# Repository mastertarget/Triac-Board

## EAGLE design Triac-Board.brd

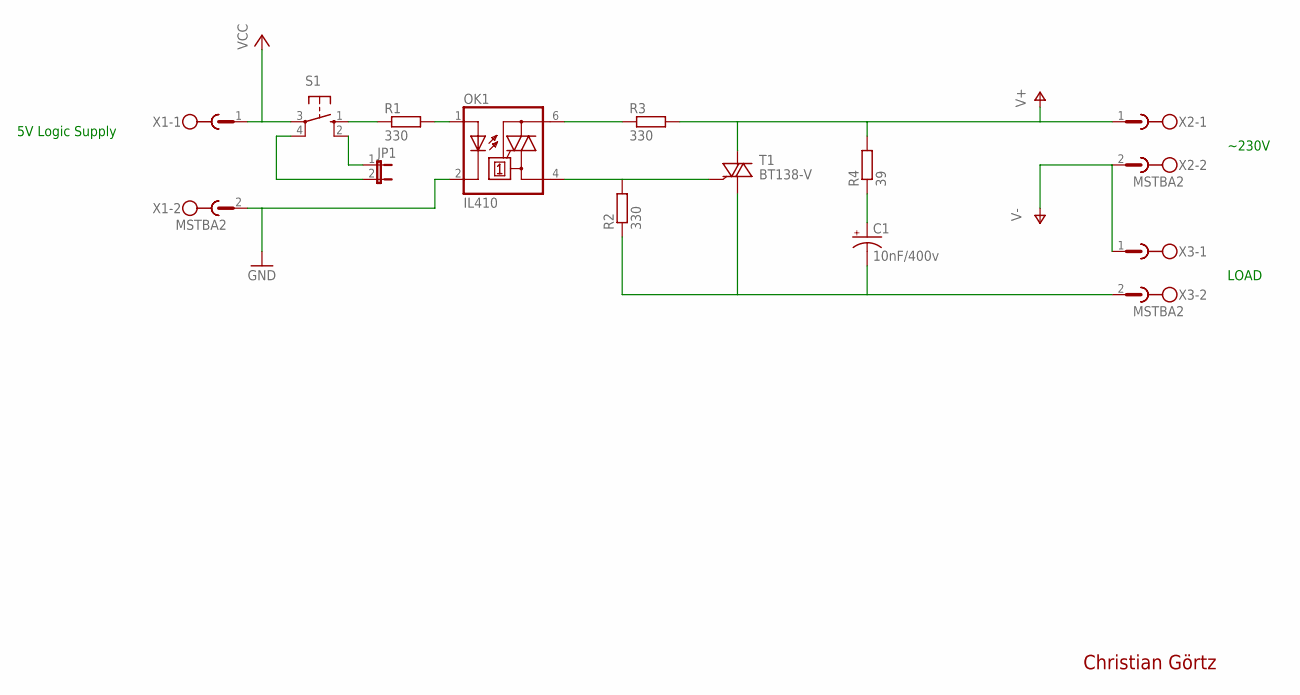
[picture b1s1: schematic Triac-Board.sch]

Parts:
C1: 10nF/400v; E5-5
JP1: JP1E; JP1
OK1: IL410; DIL06
R1, R2, R3: 330; 0207/12
R4: 39; 0207/12
S1: 10-XX; B3F-10XX
T1: BT138-V; TO220BV
X1, X2, X3: MSTBA2

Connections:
GND: OK1.2 (C), X1.2
unnamed: OK1.1 (A), R1.2
unnamed: R1.1, S1.1 (S)
unnamed: OK1.6 (A2), R3.1
unnamed: JP1.1, S1.2 (S1)
unnamed: JP1.2, S1.4 (P1)
unnamed: OK1.4 (A1), R2.2, T1.G
unnamed: C1.+, R4.1
unnamed: C1.-, R2.1, T1.T1 (A1), X3.2
V+: R3.2, R4.2, T1.T2 (A2), X2.1
V-: X2.2, X3.1
VCC: S1.3, X1.1

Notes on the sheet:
~230V
LOAD
5V Logic Supply
Christian Görtz

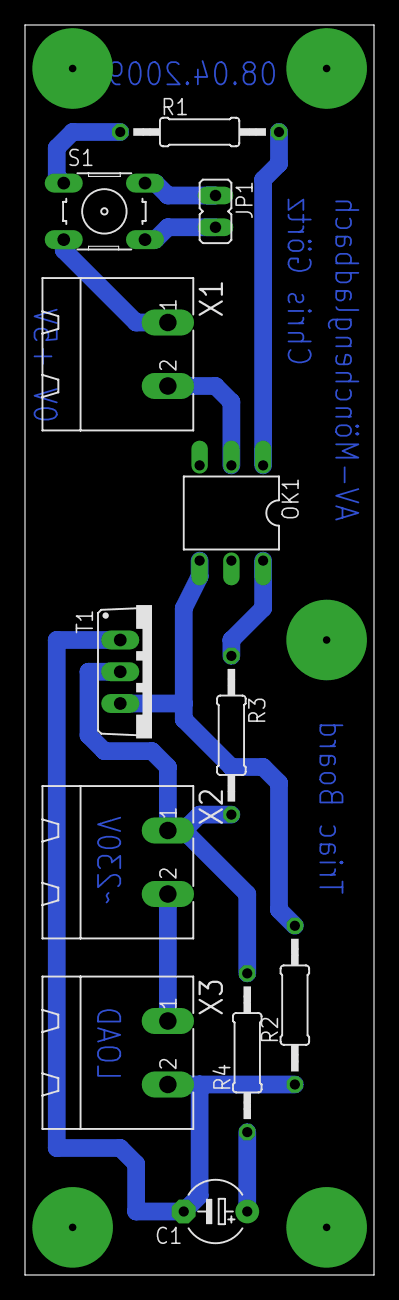
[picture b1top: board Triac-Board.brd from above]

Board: 2 copper layers, 27.9 x 100.0 mm, 12 parts (0 on the bottom side), 12 nets.

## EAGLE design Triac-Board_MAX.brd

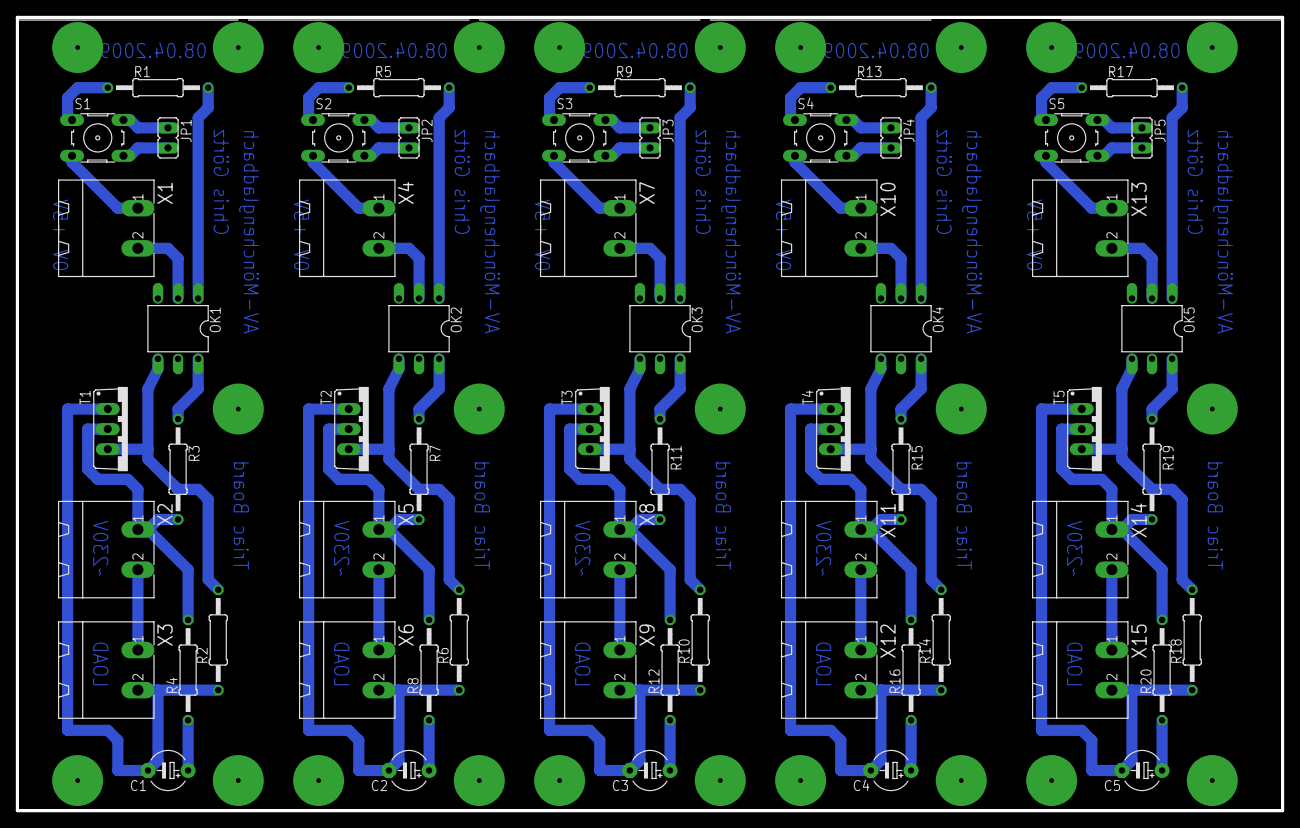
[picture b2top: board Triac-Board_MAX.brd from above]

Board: 2 copper layers, 160.0 x 100.3 mm, 60 parts (0 on the bottom side), 60 nets.

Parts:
C1, C2, C3, C4, C5: 10nF/400v; E5-5
JP1, JP2, JP3, JP4, JP5: JP1
OK1, OK2, OK3, OK4, OK5: IL410; DIL06
R1, R2, R3, R5, R6, R7, R9, R10, R11, R13, R14, R15, R17, R18, R19: 330; 0207/12
R4, R8, R12, R16, R20: 39; 0207/12
S1, S2, S3, S4, S5: B3F-10XX
T1, T2, T3, T4, T5: BT138-V; TO220BV
X1, X2, X3, X4, X5, X6, X7, X8, X9, X10, X11, X12, X13, X14, X15: MSTBA2

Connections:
GND: OK1.2, X1.2
GND1: OK2.2, X4.2
GND2: OK3.2, X7.2
GND3: OK4.2, X10.2
GND4: OK5.2, X13.2
unnamed: OK1.1, R1.2
unnamed: R1.1, S1.1
unnamed: OK1.6, R3.1
unnamed: JP1.1, S1.2
unnamed: JP1.2, S1.4
unnamed: OK1.4, R2.2, T1.G
unnamed: C1.+, R4.1
unnamed: C1.-, R2.1, T1.T1, X3.2
unnamed: OK2.1, R5.2
unnamed: R5.1, S2.1
unnamed: JP2.1, S2.2
unnamed: JP2.2, S2.4
unnamed: OK2.6, R7.1
unnamed: OK2.4, R6.2, T2.G
unnamed: C2.+, R8.1
unnamed: C2.-, R6.1, T2.T1, X6.2
unnamed: OK3.1, R9.2
unnamed: R9.1, S3.1
unnamed: JP3.1, S3.2
unnamed: JP3.2, S3.4
unnamed: OK3.6, R11.1
unnamed: OK3.4, R10.2, T3.G
unnamed: C3.+, R12.1
unnamed: C3.-, R10.1, T3.T1, X9.2
unnamed: OK4.1, R13.2
unnamed: R13.1, S4.1
unnamed: JP4.1, S4.2
unnamed: JP4.2, S4.4
unnamed: OK4.6, R15.1
unnamed: OK4.4, R14.2, T4.G
unnamed: C4.+, R16.1
unnamed: C4.-, R14.1, T4.T1, X12.2
unnamed: OK5.1, R17.2
unnamed: R17.1, S5.1
unnamed: JP5.1, S5.2
unnamed: JP5.2, S5.4
unnamed: OK5.6, R19.1
unnamed: OK5.4, R18.2, T5.G
unnamed: C5.+, R20.1
unnamed: C5.-, R18.1, T5.T1, X15.2
V+: R3.2, R4.2, T1.T2, X2.1
V+1: R7.2, R8.2, T2.T2, X5.1
V+2: R11.2, R12.2, T3.T2, X8.1
V+3: R15.2, R16.2, T4.T2, X11.1
V+4: R19.2, R20.2, T5.T2, X14.1
V-: X2.2, X3.1
V-1: X5.2, X6.1
V-2: X8.2, X9.1
V-3: X11.2, X12.1
V-4: X14.2, X15.1
VCC: S1.3, X1.1
VCC1: S2.3, X4.1
VCC2: S3.3, X7.1
VCC3: S4.3, X10.1
VCC4: S5.3, X13.1
